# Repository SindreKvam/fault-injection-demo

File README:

# README

This repository contains code used to demonstrate a voltage glitch, fault injection attack.

<center>

**Table 1:** Instruments used during testing.
| Name   | Description  |
|--------|--------------|
|        | Powersupply  |
|        | Oscilloscope |

</center>

## Fault Injection Demonstration

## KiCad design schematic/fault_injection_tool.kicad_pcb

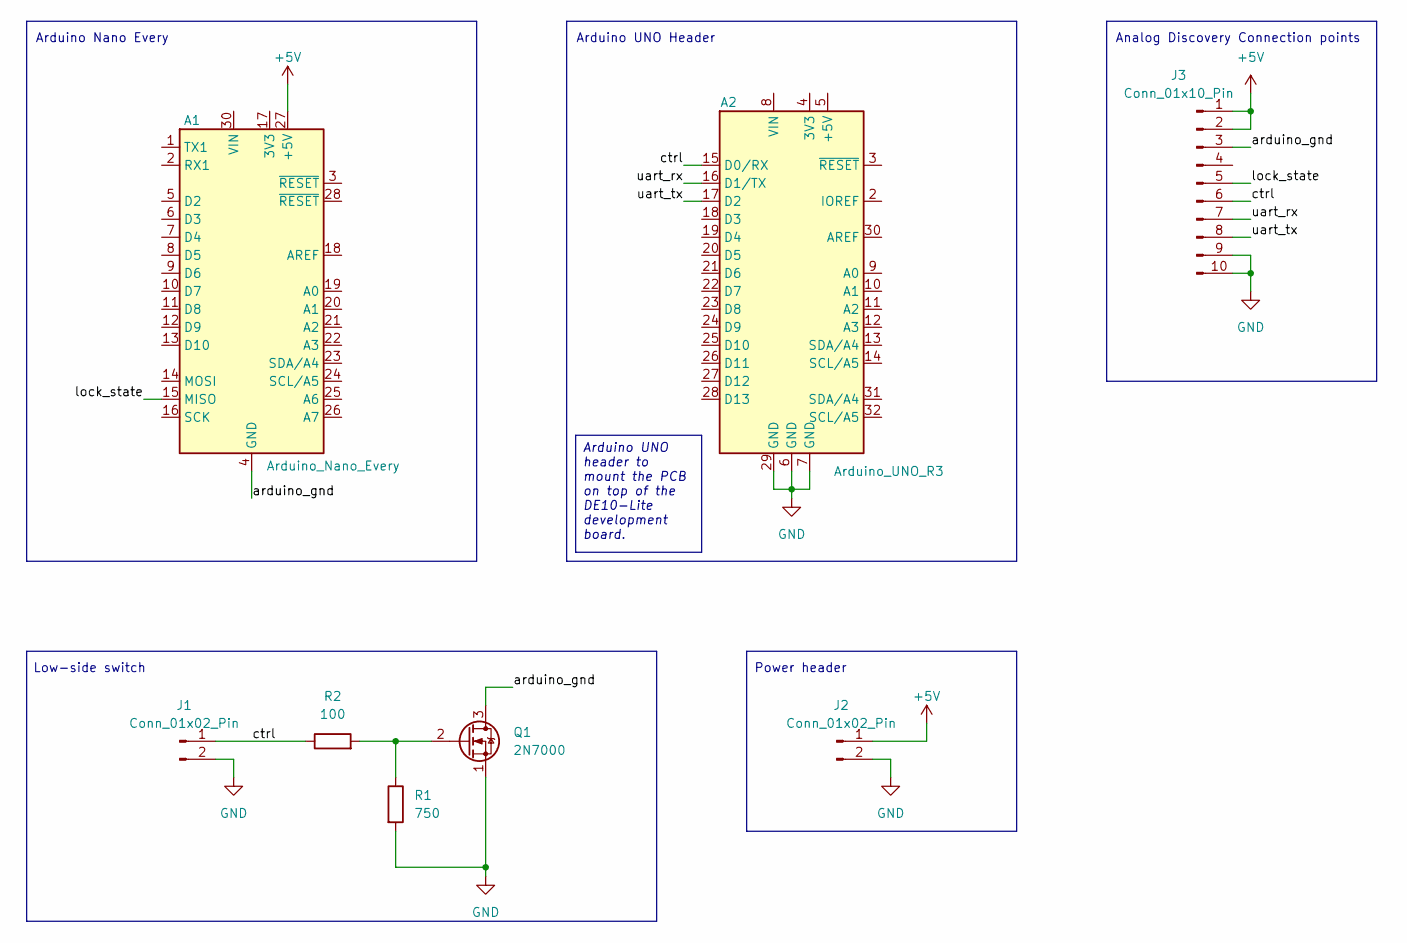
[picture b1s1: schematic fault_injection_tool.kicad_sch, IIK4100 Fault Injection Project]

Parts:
A1: Arduino_Nano_Every; Arduino_Nano
A2: Arduino_UNO_R3
J1, J2: Conn_01x02_Pin; PinHeader_1x02_P2.54mm_Vertical
J3: Conn_01x10_Pin; PinHeader_1x10_P2.54mm_Vertical
Q1: 2N7000; TO-92_Inline
R1: 750; R_0603_1608Metric_Pad0.98x0.95mm_HandSolder
R2: 100; R_0603_1608Metric_Pad0.98x0.95mm_HandSolder

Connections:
+5V: A1.27 (+5V), J2.1, J3.1, J3.2
/arduino_gnd: A1.4 (GND), A1.29 (GND), J3.3, Q1.3 (D)
/ctrl: A2.15 (D0/RX), J1.1, J3.6, R2.1
/lock_state: A1.15 (MISO), J3.5
/uart_rx: A2.16 (D1/TX), J3.7
/uart_tx: A2.17 (D2), J3.8
GND: A2.6 (GND), A2.7 (GND), A2.29 (GND), J1.2, J2.2, J3.9, J3.10, Q1.1 (S), R1.2
unnamed: Q1.2 (G), R1.1, R2.2

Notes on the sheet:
Arduino UNO Header
Arduino Nano Every
Analog Discovery Connection points
Low-side switch
Power header
Arduino UNO header to mount the PCB on top of the DE10-Lite development board.

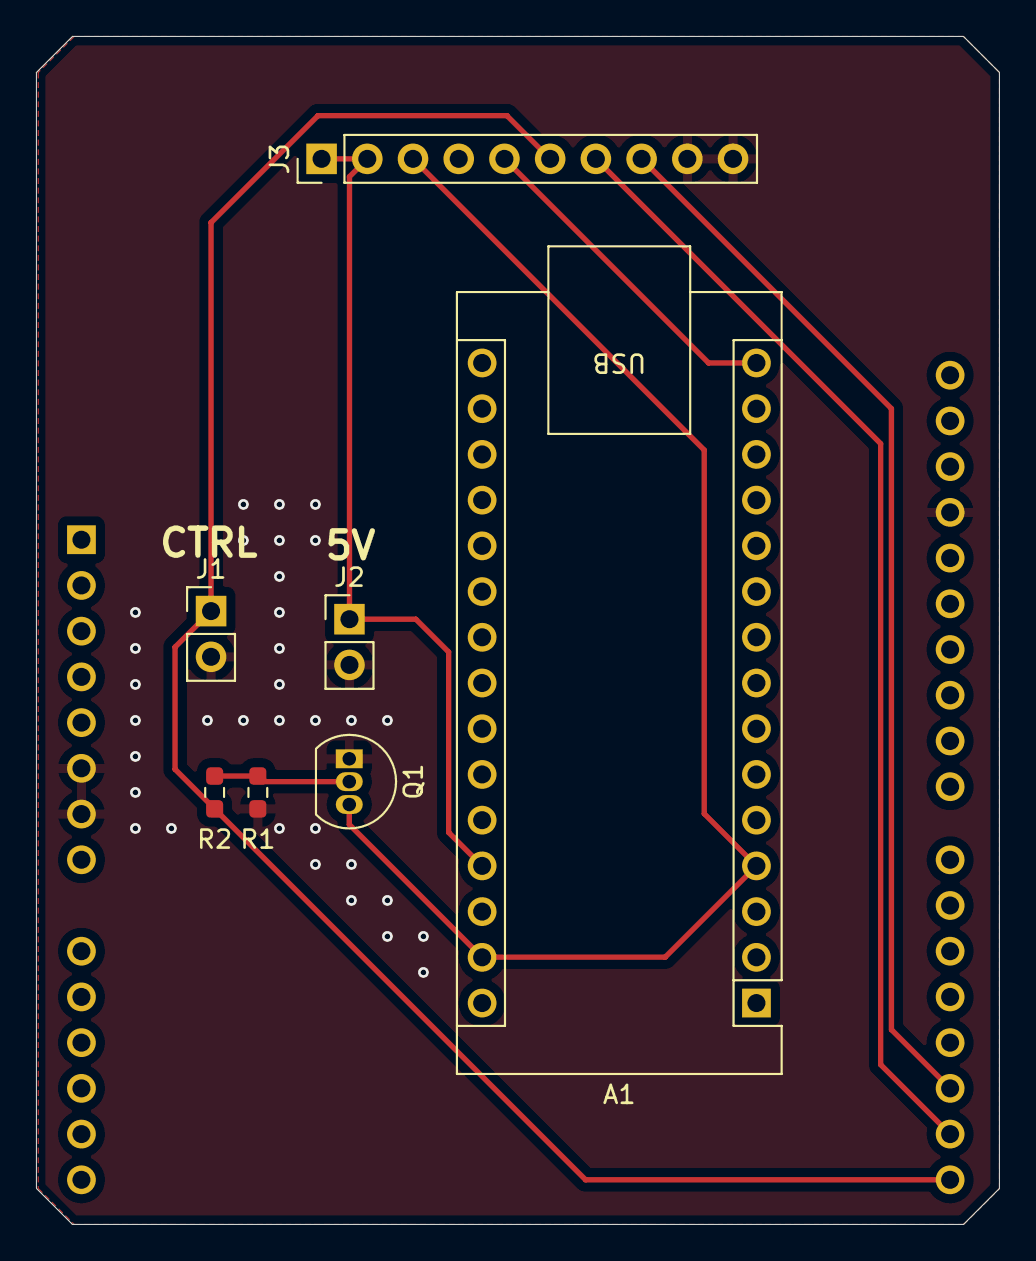
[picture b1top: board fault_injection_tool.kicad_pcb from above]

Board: 2 copper layers, 53.5 x 66.0 mm, 8 parts (1 on the bottom side), 8 nets.

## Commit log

2025-03-12 Added API for powersupply to control power to the DUT
2025-03-12 Updated gitignore
2025-03-12 Added simulation of comparator circuit for power delivery to arduino
2025-03-15 Added quartus project files
2025-03-15 Removed .tcl file dependency
2025-03-16 Updated arduino code, now using pins to indicate if hack has been performed
2025-03-16 Added various simulations, found circuit that works nicely
2025-03-16 Initial commit of fault injection tool schematic
2025-03-16 Create LICENSE
2025-03-17 Added uart_regs tool
2025-03-17 Added generated uart register files
2025-03-17 Updated project files
2025-03-17 Removed dependency of dp file
2025-03-17 Updated top level to match rest of the system
2025-03-17 Updated arduino firmware
2025-03-17 Updated simulation file
2025-03-17 Updated schematic drawing and PCB design
2025-03-17 Added extra register that can be accessed using UART
2025-03-18 Made some changes to the schematic
2025-03-22 Added script to run attacks with parameters, as well as attack sweeps.
2025-03-24 Removed dependencies
2025-03-24 Updated script to run attack to also add delayed lock state to find if device reset. Added script to analyze data
2025-03-24 Update top level to check for rising edge of start_glitch signal
2025-03-24 Updated schematic and pcb layout
2025-03-24 Added script to plot simulated data from LTspice
2025-03-24 Updated plotting in analyze_attacks
2025-03-24 Added analog discovery workspace for quick setup
